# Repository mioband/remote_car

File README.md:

# remote_car
Данный репозиторий содержит код для модуля машинки для управления с браслета
## Ветки
В данном репозитории две основные ветки:
### main
Главная ветка со стабильной версией ПО. Здесь всегда должен быть чистый и рабочий код, а также вся документация. 
### develop
Ветка разработки. Здесь находятся тестовые и разрабатываемые версии кода.

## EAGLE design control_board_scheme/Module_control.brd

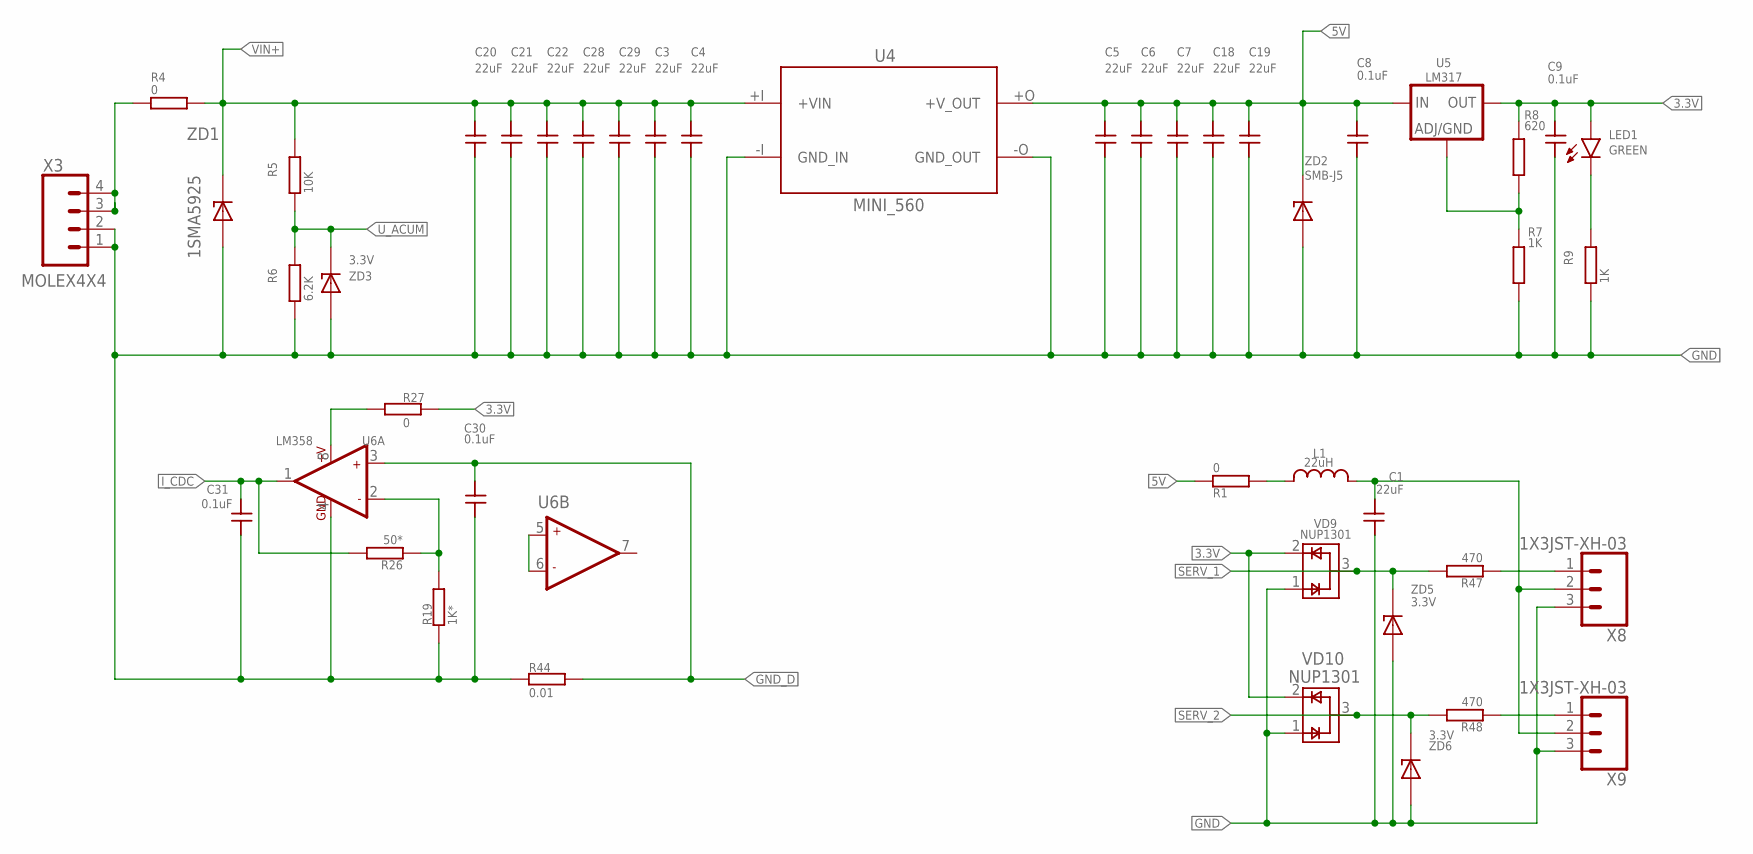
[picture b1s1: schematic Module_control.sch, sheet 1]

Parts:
C1, C3, C4, C5, C6, C7, C18, C19, C20, C21, C22, C28, C29: 22uF; 1206; VOLTAGE 16V
C8, C9, C30, C31: 0.1uF; 0603; VOLTAGE 16V
L1: 22uH; 0420CDMC
LED1: GREEN; 1608
R1, R27: 0; 0603
R4: 0; 2512
R5: 10K; 0603
R6: 6.2K; 0603
R7, R9: 1K; 0603
R8: 620; 0603
R19: 1K*; 0603
R26: 50*; 0603
R44: 0.01; 1206
R47, R48: 470; 0603
U4: MINI_560; MINI560_OTB
U5: LM317; D-PAK
U6: LM358; SOIC-8
VD9, VD10: NUP1301; SOT23
X3: MOLEX4X4; MOLEX-2X2U
X8, X9: 1X3JST-XH-03; JST-XH-03
ZD1: 1SMA5925; SMB
ZD2: SMB-J5; SMB
ZD3, ZD5, ZD6: 3.3V; MINIMELF

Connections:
3.3V: C9.P$2, LED1.P$2 (A), R8.P$2, R27.P$2, U5.4 (OUT), VD9.2 (VCC), VD10.2 (VCC); also elsewhere on the board
5: L1.2, R1.P$2
5V: C5.P$2, C6.P$2, C7.P$2, C8.P$2, C18.P$2, C19.P$2, R1.P$1, U4.+O (+V_OUT), U5.3 (IN), ZD2.C; also elsewhere on the board
GND: C1.P$1, C3.P$1, C4.P$1, C5.P$1, C6.P$1, C7.P$1, C8.P$1, C9.P$1, C18.P$1, C19.P$1, C20.P$1, C21.P$1, C22.P$1, C28.P$1, C29.P$1, C30.P$1, C31.P$1, R6.P$1, R7.P$2, R9.P$1, R19.P$1, R44.P$1, U4.-I (GND_IN), U4.-O (GND_OUT), U6.4 (GND), VD9.1 (GND), VD10.1 (GND), X3.1, X3.2, X8.3, X9.3, ZD1.A, ZD2.A, ZD3.A, ZD5.A, ZD6.A; also elsewhere on the board
GND_D: C30.P$2, R44.P$2, U6.3 (+IN1); also elsewhere on the board
I_CDC: C31.P$2, R26.P$2, U6.1 (OUT1); also elsewhere on the board
unnamed: R48.P$1, X9.1
unnamed: R7.P$1, R8.P$1, U5.1 (ADJ/GND)
unnamed: LED1.P$1 (C), R9.P$2
unnamed: R4.1, X3.3, X3.4
unnamed: R47.P$1, X8.1
unnamed: R19.P$2, R26.P$1, U6.2 (-IN1)
unnamed: U6.5 (+IN2), U6.6 (-IN2)
SERV_1: R47.P$2, VD9.3 (I/O), ZD5.C; also elsewhere on the board
SERV_2: R48.P$2, VD10.3 (I/O), ZD6.C; also elsewhere on the board
U_ACUM: R5.P$1, R6.P$2, ZD3.C; also elsewhere on the board
V+: R27.P$1, U6.8 (+V)
VIN+: C3.P$2, C4.P$2, C20.P$2, C21.P$2, C22.P$2, C28.P$2, C29.P$2, R4.2, R5.P$2, U4.+I (+VIN), ZD1.C; also elsewhere on the board
VSERV: C1.P$2, L1.1, X8.2, X9.2

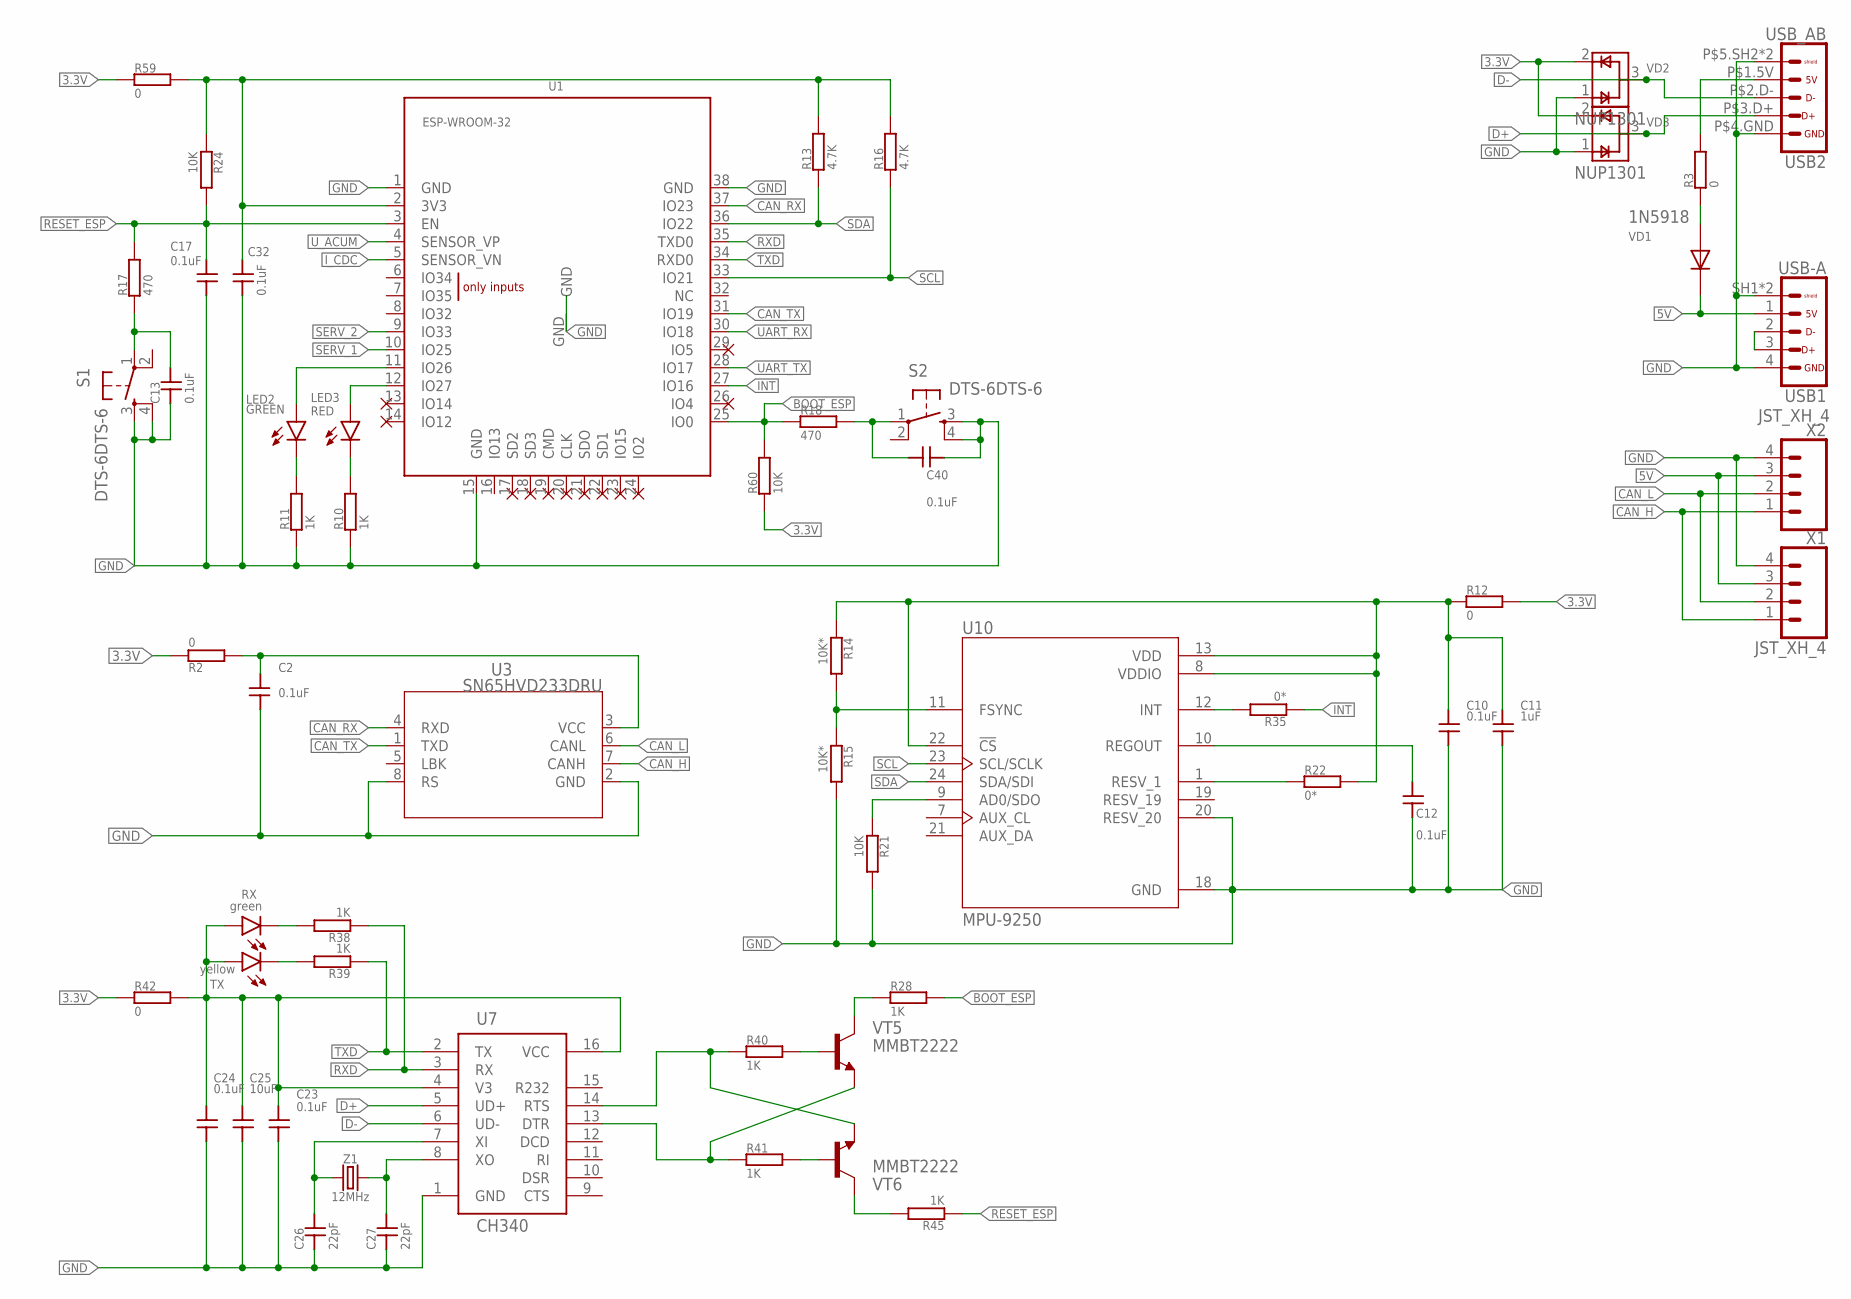
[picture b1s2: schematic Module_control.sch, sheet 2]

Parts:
C2, C10, C12, C13, C17, C23, C24, C32, C40: 0.1uF; 0603; VOLTAGE 16V
C11: 1uF; 0603; VOLTAGE 16V
C25: 10uF; 0603; VOLTAGE 16V
C26, C27: 22pF; 0603; VOLTAGE 6.3V
LED2: GREEN; 1608
LED3: RED; 1608
R2, R3, R12, R42, R59: 0; 0603
R10, R11, R28, R38, R39, R40, R41, R45: 1K; 0603
R13, R16: 4.7K; 0603
R14, R15: 10K*; 0603
R17, R18: 470; 0603
R21, R24, R60: 10K; 0603
R22, R35: 0*; 0603
RX: green; 2013
S1, S2: DTS-6DTS-6; DTS-6
TX: yellow; 2013
U1: ESP-WROOM-32
U3: SN65HVD233DRU; SOIC-8
U7: CH340; SOIC-16
U10: MPU-9250; QFN40P300X300X105-24N
USB1: USB-A; A-VERTICAL
USB2: USB_AB; B-VERTICAL
VD1: 1N5918; SOD123
VD2, VD3: NUP1301; SOT23
VT5, VT6: MMBT2222; SOT-23
X1, X2: JST_XH_4; JST-XH-04
Z1: 12MHz; CRYSTAL-SMD-3.2X2.5MM

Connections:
3.3V: R2.P$1, R12.P$2, R42.P$1, R59.P$1, R60.P$1, VD2.2 (VCC), VD3.2 (VCC); also elsewhere on the board
5V: USB1.1, VD1.C, X1.3, X2.3; also elsewhere on the board
+3.3: C2.P$2, R2.P$2, U3.3 (VCC)
+3V: C10.P$2, C11.P$2, R12.P$1, R14.P$1, R22.P$2, U10.8 (VDDIO), U10.13 (VDD), U10.22 (!CS)
BOOT_ESP: R18.P$1, R28.P$2, R60.P$2, U1.25 (IO0)
CAN_H: U3.7 (CANH), X1.1, X2.1
CAN_L: U3.6 (CANL), X1.2, X2.2
CAN_RX: U1.37 (IO23), U3.4 (RXD)
CAN_TX: U1.31 (IO19), U3.1 (TXD)
D+: U7.5 (UD+), USB2.P$3.D+ (3), VD3.3 (I/O)
D-: U7.6 (UD-), USB2.P$2.D- (2), VD2.3 (I/O)
DTR: R41.P$1, U7.13 (DTR), VT5.2 (E)
ESP_3.3V: C32.P$2, R13.P$2, R16.P$2, R24.P$1, R59.P$2, U1.2 (3V3)
GND: C2.P$1, C10.P$1, C11.P$1, C12.P$1, C13.P$1, C17.P$1, C23.P$1, C24.P$1, C25.P$1, C26.P$1, C27.P$1, C32.P$1, C40.P$1, R10.P$1, R11.P$1, R15.P$2, R21.P$2, S1.3, S1.4, S2.3, S2.4, U1.1 (GND), U1.15 (GND), U1.38 (GND), U1.GND, U3.2 (GND), U3.8 (RS), U7.1 (GND), U10.18 (GND), U10.20 (RESV_20), USB1.4, USB1.SH1 (SHIELD), USB1.SH2 (SHIELD), USB2.P$4.GND (4), USB2.P$5.SH2 (SHIELD), USB2.P$6.SH1 (SHIELD), VD2.1 (GND), VD3.1 (GND), X1.4, X2.4; also elsewhere on the board
INT: R35.P$1, U1.27 (IO16)
IT: R35.P$2, U10.12 (INT)
I_CDC: U1.5 (SENSOR_VN); also elsewhere on the board
unnamed: C40.P$2, R18.P$2, S2.1
unnamed: R3.P$2, USB2.P$1.5V (1)
unnamed: USB1.2, USB1.3
unnamed: R3.P$1, VD1.A
unnamed: LED2.P$2 (A), U1.11 (IO26)
unnamed: LED3.P$2 (A), U1.12 (IO27)
unnamed: LED3.P$1 (C), R10.P$2
unnamed: LED2.P$1 (C), R11.P$2
unnamed: R21.P$1, U10.9 (AD0/SDO)
unnamed: C12.P$2, U10.10 (REGOUT)
unnamed: R22.P$1, U10.1 (RESV_1)
unnamed: R38.P$2, RX.P$1 (C)
unnamed: R14.P$2, R15.P$1, U10.11 (FSYNC)
unnamed: R39.P$2, TX.P$1 (C)
unnamed: C27.P$2, U7.8 (XO), Z1.3 (2)
unnamed: C26.P$2, U7.7 (XI), Z1.1
unnamed: R40.P$2, VT5.1 (B)
unnamed: R41.P$2, VT6.1 (B)
unnamed: R28.P$1, VT5.3 (C)
unnamed: R45.P$2, VT6.3 (C)
unnamed: C13.P$2, R17.P$1, S1.1
RESET_ESP: C17.P$2, R17.P$2, R24.P$2, R45.P$1, U1.3 (EN)
RTS: R40.P$1, U7.14 (RTS), VT6.2 (E)
RXD: R38.P$1, U1.35 (TXD0), U7.3 (RX)
SCL: R16.P$1, U1.33 (IO21), U10.23 (SCL/SCLK)
SDA: R13.P$1, U1.36 (IO22), U10.24 (SDA/SDI)
SERV_1: U1.10 (IO25); also elsewhere on the board
SERV_2: U1.9 (IO33); also elsewhere on the board
TXD: R39.P$1, U1.34 (RXD0), U7.2 (TX)
UART_RX: U1.30 (IO18); also elsewhere on the board
UART_TX: U1.28 (IO17); also elsewhere on the board
U_ACUM: U1.4 (SENSOR_VP); also elsewhere on the board
VCC: C23.P$2, C24.P$2, C25.P$2, R42.P$2, RX.P$2 (A), TX.P$2 (A), U7.4 (V3), U7.16 (VCC)

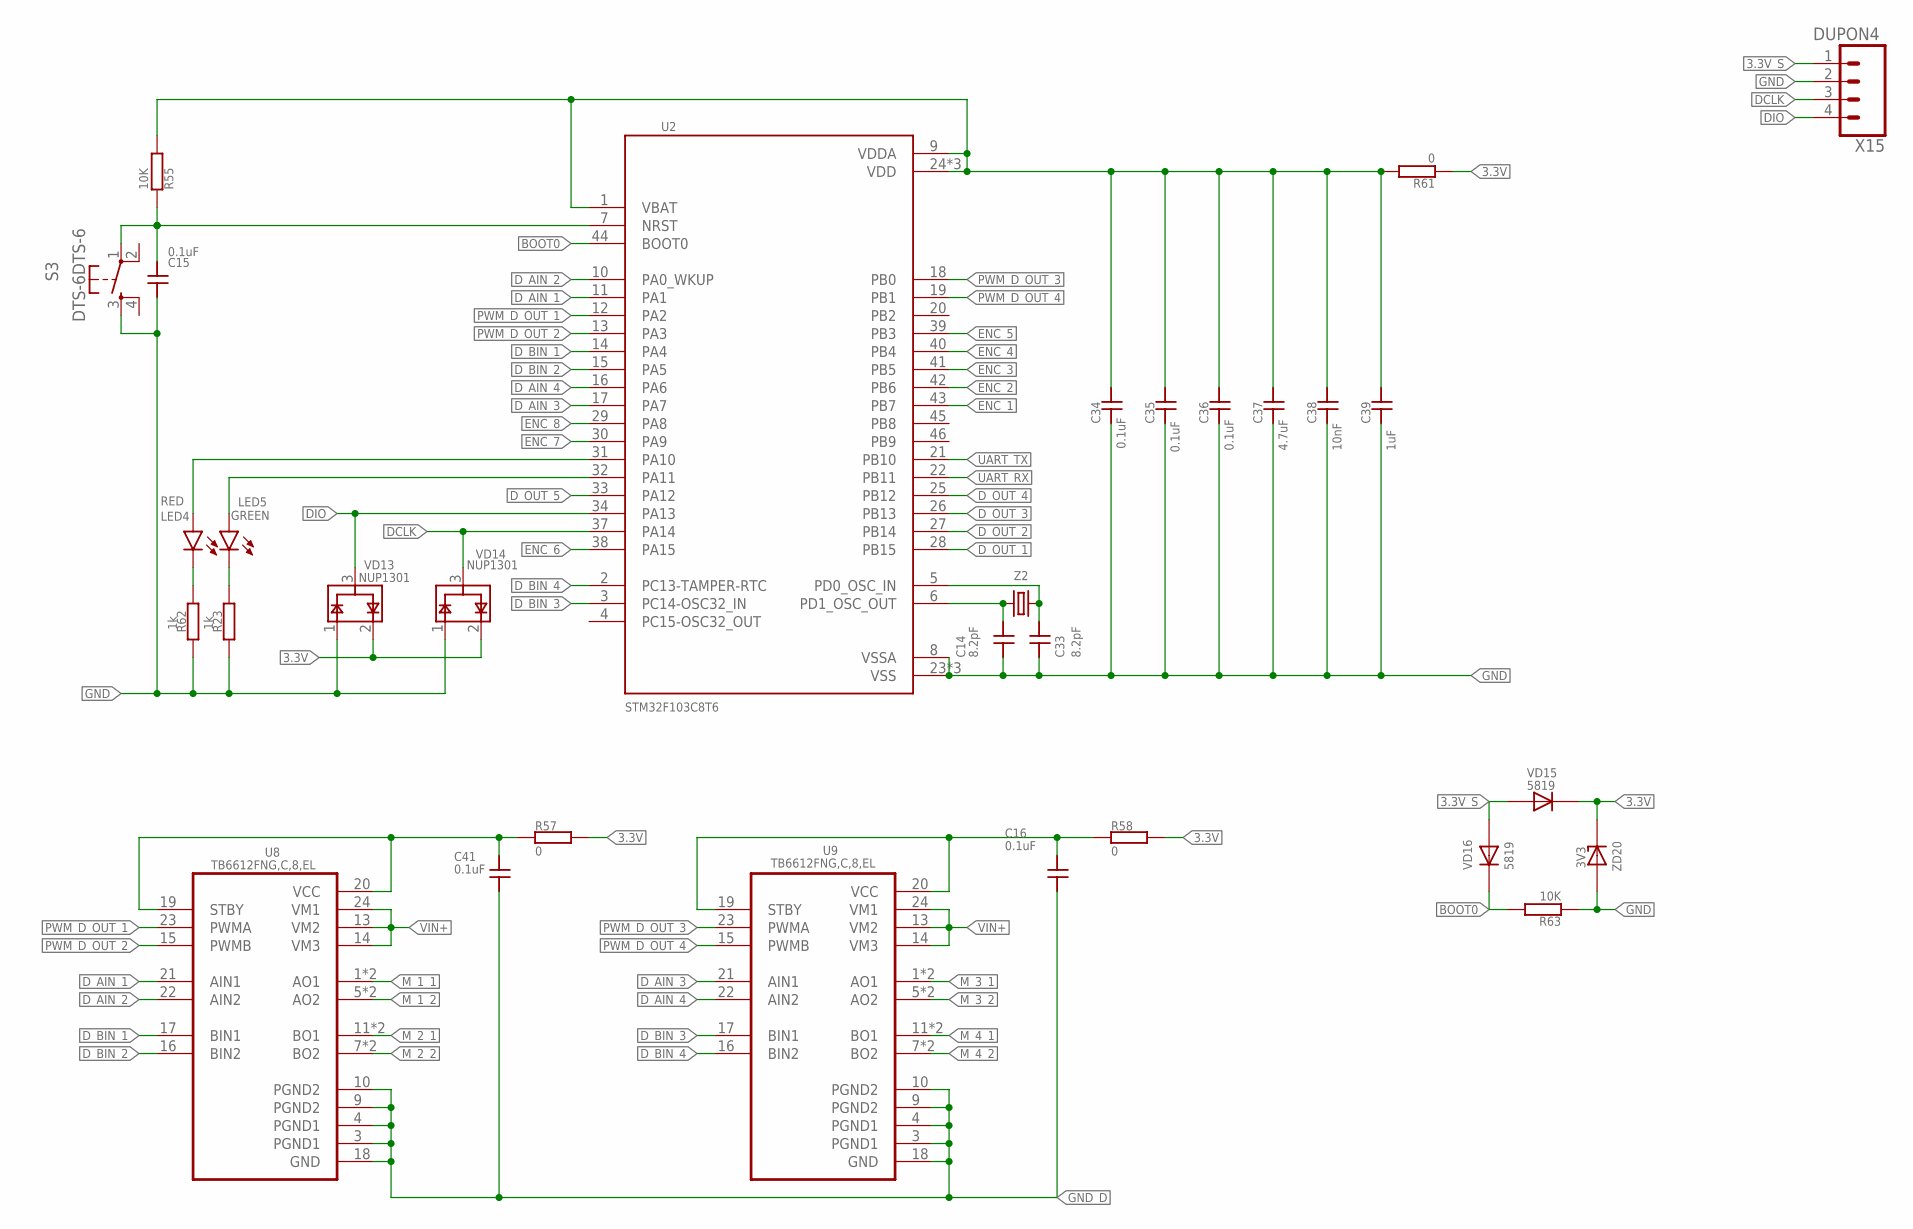
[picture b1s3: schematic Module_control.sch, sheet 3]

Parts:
C14, C33: 8.2pF; 0603; VOLTAGE 16V
C15, C16, C34, C35, C36, C41: 0.1uF; 0603; VOLTAGE 16V
C37: 4.7uF; 0603; VOLTAGE 16V
C38: 10nF; 0603; VOLTAGE 16V
C39: 1uF; 0603; VOLTAGE 16V
LED4: RED; 1608
LED5: GREEN; 1608
R23, R62: 1k; 0603
R55, R63: 10K; 0603
R57, R58, R61: 0; 0603
S3: DTS-6DTS-6; DTS-6
U2: STM32F103C8T6; QFP50P900X900X160-48N
U8, U9: TB6612FNG,C,8,EL; SOP65
VD13, VD14: NUP1301; SOT23
VD15, VD16: 5819; SOD123
X15: DUPON4; 1X04DUPON
Z2: 8MHz; CRYSTAL-SMD-3.2X2.5MM
ZD20: 3V3; MINIMELF

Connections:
3.3V: R57.P$2, R58.P$2, R61.P$1, VD13.2 (VCC), VD14.2 (VCC), VD15.C, ZD20.C; also elsewhere on the board
3.3V_S: VD15.A, VD16.A, X15.1
+VC: C41.P$2, R57.P$1, U8.19 (STBY), U8.20 (VCC)
BOOT0: R63.P$2, U2.44 (BOOT0), VD16.C
DCLK: U2.37 (PA14), VD14.3 (I/O), X15.3
DIO: U2.34 (PA13), VD13.3 (I/O), X15.4
D_AIN_1: U2.11 (PA1), U8.21 (AIN1)
D_AIN_2: U2.10 (PA0_WKUP), U8.22 (AIN2)
D_AIN_3: U2.17 (PA7), U9.21 (AIN1)
D_AIN_4: U2.16 (PA6), U9.22 (AIN2)
D_BIN_1: U2.14 (PA4), U8.17 (BIN1)
D_BIN_2: U2.15 (PA5), U8.16 (BIN2)
D_BIN_3: U2.3 (PC14-OSC32_IN), U9.17 (BIN1)
D_BIN_4: U2.2 (PC13-TAMPER-RTC), U9.16 (BIN2)
D_OUT_1: U2.28 (PB15); also elsewhere on the board
D_OUT_2: U2.27 (PB14); also elsewhere on the board
D_OUT_3: U2.26 (PB13); also elsewhere on the board
D_OUT_4: U2.25 (PB12); also elsewhere on the board
D_OUT_5: U2.33 (PA12); also elsewhere on the board
ENC_1: U2.43 (PB7); also elsewhere on the board
ENC_2: U2.42 (PB6); also elsewhere on the board
ENC_3: U2.41 (PB5); also elsewhere on the board
ENC_4: U2.40 (PB4); also elsewhere on the board
ENC_5: U2.39 (PB3); also elsewhere on the board
ENC_6: U2.38 (PA15); also elsewhere on the board
ENC_7: U2.30 (PA9); also elsewhere on the board
ENC_8: U2.29 (PA8); also elsewhere on the board
GND: C14.P$1, C15.P$2, C33.P$1, C34.P$1, C35.P$1, C36.P$1, C37.P$1, C38.P$1, C39.P$1, R23.P$2, R62.P$2, R63.P$1, S3.3, U2.8 (VSSA), U2.23 (VSS), U2.35 (VSS), U2.47 (VSS), VD13.1 (GND), VD14.1 (GND), X15.2, ZD20.A; also elsewhere on the board
GND_D: C16.P$1, C41.P$1, U8.3 (PGND1), U8.4 (PGND1), U8.9 (PGND2), U8.10 (PGND2), U8.18 (GND), U9.3 (PGND1), U9.4 (PGND1), U9.9 (PGND2), U9.10 (PGND2), U9.18 (GND); also elsewhere on the board
M_1_1: U8.1 (AO1), U8.2 (AO1); also elsewhere on the board
M_1_2: U8.5 (AO2), U8.6 (AO2); also elsewhere on the board
M_2_1: U8.11 (BO1), U8.12 (BO1); also elsewhere on the board
M_2_2: U8.7 (BO2), U8.8 (BO2); also elsewhere on the board
M_3_1: U9.1 (AO1), U9.2 (AO1); also elsewhere on the board
M_3_2: U9.5 (AO2), U9.6 (AO2); also elsewhere on the board
M_4_1: U9.11 (BO1), U9.12 (BO1); also elsewhere on the board
M_4_2: U9.7 (BO2), U9.8 (BO2); also elsewhere on the board
unnamed: LED4.P$1 (C), R62.P$1
unnamed: C16.P$2, R58.P$1, U9.19 (STBY), U9.20 (VCC)
unnamed: LED5.P$1 (C), R23.P$1
unnamed: LED4.P$2 (A), U2.31 (PA10)
unnamed: LED5.P$2 (A), U2.32 (PA11)
unnamed: C14.P$2, U2.6 (PD1_OSC_OUT), Z2.1
unnamed: C33.P$2, U2.5 (PD0_OSC_IN), Z2.3 (2)
NRST: C15.P$1, R55.P$1, S3.1, U2.7 (NRST)
PWM_D_OUT_1: U2.12 (PA2), U8.23 (PWMA)
PWM_D_OUT_2: U2.13 (PA3), U8.15 (PWMB)
PWM_D_OUT_3: U2.18 (PB0), U9.23 (PWMA)
PWM_D_OUT_4: U2.19 (PB1), U9.15 (PWMB)
UART_RX: U2.22 (PB11); also elsewhere on the board
UART_TX: U2.21 (PB10); also elsewhere on the board
VDD1: C34.P$2, C35.P$2, C36.P$2, C37.P$2, C38.P$2, C39.P$2, R55.P$2, R61.P$2, U2.1 (VBAT), U2.9 (VDDA), U2.24 (VDD), U2.36 (VDD), U2.48 (VDD)
VIN+: U8.13 (VM2), U8.14 (VM3), U8.24 (VM1), U9.13 (VM2), U9.14 (VM3), U9.24 (VM1); also elsewhere on the board

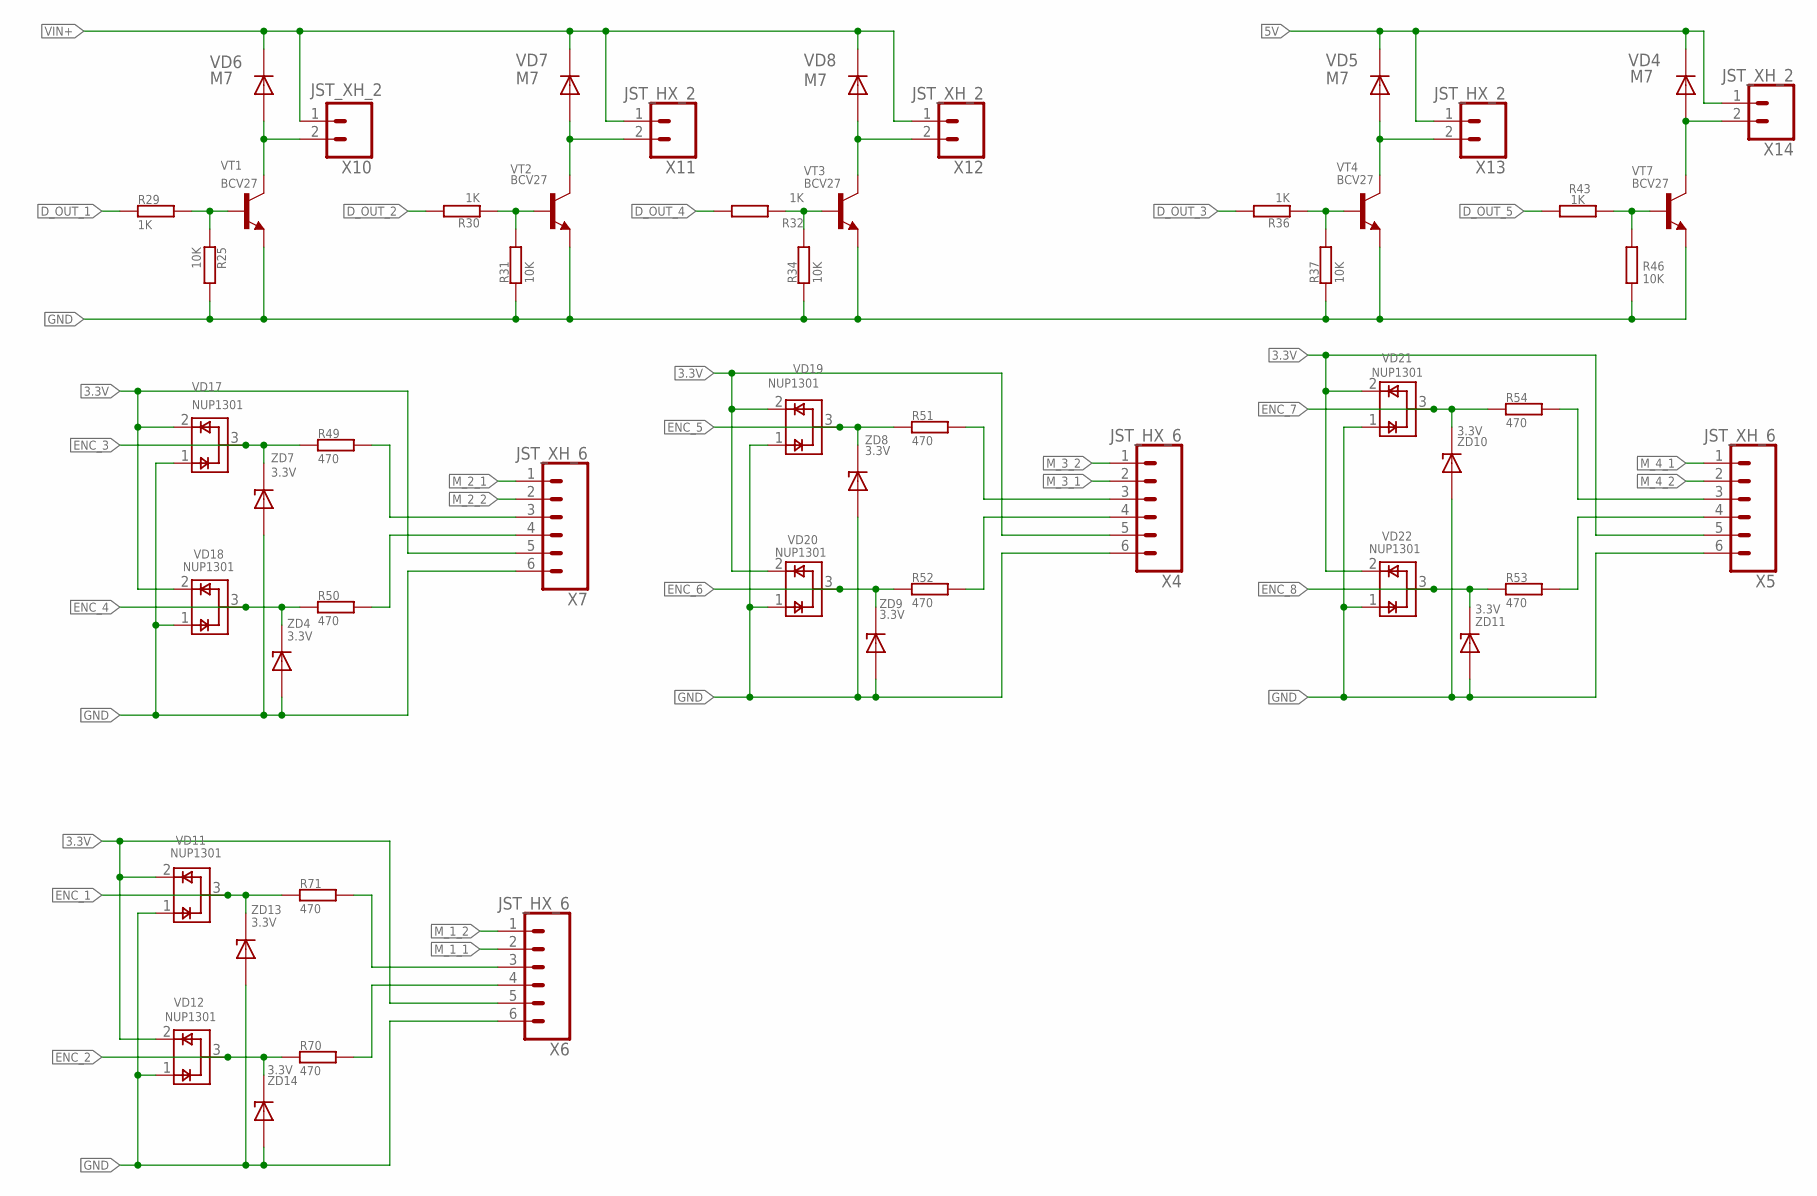
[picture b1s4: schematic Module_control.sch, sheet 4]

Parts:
R25, R31, R34, R37, R46: 10K; 0603
R29, R30, R32, R36, R43: 1K; 0603
R49, R50, R51, R52, R53, R54, R70, R71: 470; 0603
VD4, VD5, VD6, VD7, VD8: M7; SMA
VD11, VD12, VD17, VD18, VD19, VD20, VD21, VD22: NUP1301; SOT23
VT1, VT2, VT3, VT4, VT7: BCV27; SOT-23
X4, X6: JST_HX_6; JST-XH-06
X5, X7: JST_XH_6; JST-XH-06
X10, X12, X14: JST_XH_2; JST-XH-02
X11, X13: JST_HX_2; JST-XH-02
ZD4, ZD7, ZD8, ZD9, ZD10, ZD11, ZD13, ZD14: 3.3V; MINIMELF

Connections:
3.3V: VD11.2 (VCC), VD12.2 (VCC), VD17.2 (VCC), VD18.2 (VCC), VD19.2 (VCC), VD20.2 (VCC), VD21.2 (VCC), VD22.2 (VCC), X4.5, X5.5, X6.5, X7.5; also elsewhere on the board
5V: VD4.C, VD5.C, X13.1, X14.1; also elsewhere on the board
D_OUT_1: R29.P$1; also elsewhere on the board
D_OUT_2: R30.P$2; also elsewhere on the board
D_OUT_3: R36.P$2; also elsewhere on the board
D_OUT_4: R32.P$2; also elsewhere on the board
D_OUT_5: R43.P$2; also elsewhere on the board
ENC1: R71.P$2, X6.3
ENC2: R70.P$2, X6.4
ENC3: R49.P$2, X7.3
ENC4: R50.P$2, X7.4
ENC5: R51.P$2, X4.3
ENC6: R52.P$2, X4.4
ENC7: R54.P$2, X5.3
ENC8: R53.P$2, X5.4
ENC_1: R71.P$1, VD11.3 (I/O), ZD13.C; also elsewhere on the board
ENC_2: R70.P$1, VD12.3 (I/O), ZD14.C; also elsewhere on the board
ENC_3: R49.P$1, VD17.3 (I/O), ZD7.C; also elsewhere on the board
ENC_4: R50.P$1, VD18.3 (I/O), ZD4.C; also elsewhere on the board
ENC_5: R51.P$1, VD19.3 (I/O), ZD8.C; also elsewhere on the board
ENC_6: R52.P$1, VD20.3 (I/O), ZD9.C; also elsewhere on the board
ENC_7: R54.P$1, VD21.3 (I/O), ZD10.C; also elsewhere on the board
ENC_8: R53.P$1, VD22.3 (I/O), ZD11.C; also elsewhere on the board
GND: R25.P$2, R31.P$1, R34.P$1, R37.P$1, R46.P$1, VD11.1 (GND), VD12.1 (GND), VD17.1 (GND), VD18.1 (GND), VD19.1 (GND), VD20.1 (GND), VD21.1 (GND), VD22.1 (GND), VT1.2 (E), VT2.2 (E), VT3.2 (E), VT4.2 (E), VT7.2 (E), X4.6, X5.6, X6.6, X7.6, ZD4.A, ZD7.A, ZD8.A, ZD9.A, ZD10.A, ZD11.A, ZD13.A, ZD14.A; also elsewhere on the board
M_1_1: X6.2; also elsewhere on the board
M_1_2: X6.1; also elsewhere on the board
M_2_1: X7.1; also elsewhere on the board
M_2_2: X7.2; also elsewhere on the board
M_3_1: X4.2; also elsewhere on the board
M_3_2: X4.1; also elsewhere on the board
M_4_1: X5.1; also elsewhere on the board
M_4_2: X5.2; also elsewhere on the board
unnamed: R25.P$1, R29.P$2, VT1.1 (B)
unnamed: VD6.A, VT1.3 (C), X10.2
unnamed: R30.P$1, R31.P$2, VT2.1 (B)
unnamed: R36.P$1, R37.P$2, VT4.1 (B)
unnamed: VD7.A, VT2.3 (C), X11.2
unnamed: VD8.A, VT3.3 (C), X12.2
unnamed: VD5.A, VT4.3 (C), X13.2
unnamed: R32.P$1, R34.P$2, VT3.1 (B)
unnamed: R43.P$1, R46.P$2, VT7.1 (B)
unnamed: VD4.A, VT7.3 (C), X14.2
VIN+: VD6.C, VD7.C, VD8.C, X10.1, X11.1, X12.1; also elsewhere on the board

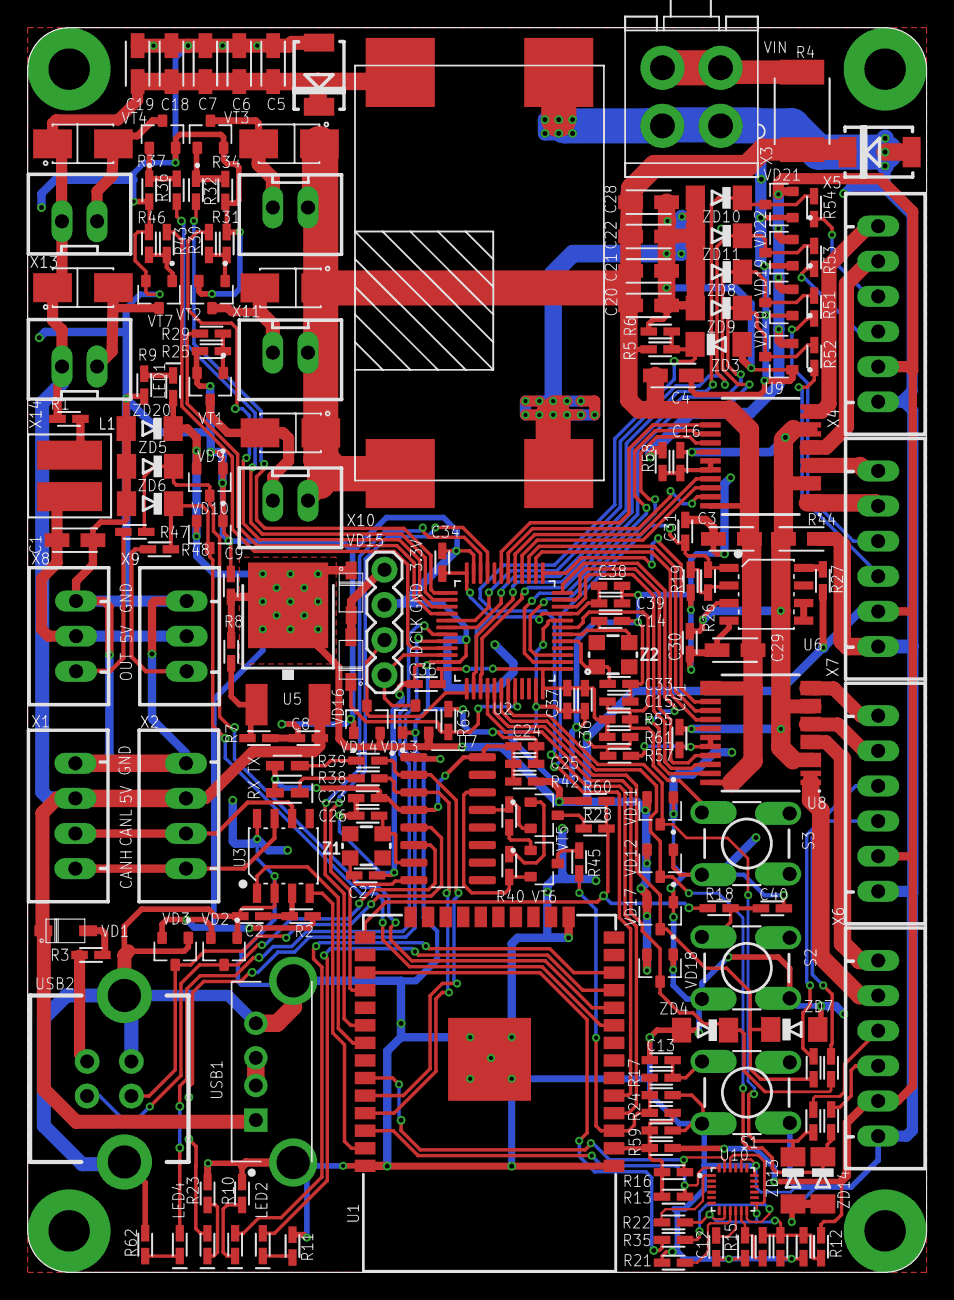
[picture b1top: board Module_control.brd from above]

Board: 2 copper layers, 65.0 x 90.0 mm, 186 parts (0 on the bottom side), 127 nets.

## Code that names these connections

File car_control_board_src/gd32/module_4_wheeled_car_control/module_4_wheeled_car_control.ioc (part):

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Mcu.Name=STM32F103C(8-B)Tx
Mcu.Package=LQFP48
Mcu.UserName=STM32F103C8Tx
PA0-WKUP.GPIOParameters=GPIO_Label
PA0-WKUP.GPIO_Label=DIG_AIN_2
PA0-WKUP.Signal=GPIO_Output
PA1.GPIOParameters=GPIO_Label
PA1.GPIO_Label=DIG_AIN_1
PA1.Signal=GPIO_Output
PA10.GPIOParameters=GPIO_Label
PA10.GPIO_Label=LED_2
PA10.Signal=GPIO_Output
PA11.GPIOParameters=GPIO_Label
PA11.GPIO_Label=LED_1
PA11.Signal=GPIO_Output
PA12.GPIOParameters=GPIO_Label
PA12.GPIO_Label=DIG_OUT_5
PA12.Signal=GPIO_Output
PA13.Mode=Serial_Wire
PA13.Signal=SYS_JTMS-SWDIO
PA14.Mode=Serial_Wire
PA14.Signal=SYS_JTCK-SWCLK
PA15.GPIOParameters=GPIO_Label
PA15.GPIO_Label=ENC_6
PA15.Signal=GPIO_Input
PA2.Signal=S_TIM2_CH3
PA3.Signal=S_TIM2_CH4
PA4.GPIOParameters=GPIO_Label
PA4.GPIO_Label=DIG_BIN_1
PA4.Signal=GPIO_Output
PA5.GPIOParameters=GPIO_Label
PA5.GPIO_Label=DIG_BIN_2
PA5.Signal=GPIO_Output
PA6.GPIOParameters=GPIO_Label
PA6.GPIO_Label=DIG_AIN_4
PA6.Signal=GPIO_Output
PA7.GPIOParameters=GPIO_Label
PA7.GPIO_Label=DIG_AIN_3
PA7.Signal=GPIO_Output
PA8.GPIOParameters=GPIO_Label
PA8.GPIO_Label=ENC_8
PA8.Signal=GPIO_Input
PA9.GPIOParameters=GPIO_Label
PA9.GPIO_Label=ENC_7
PA9.Signal=GPIO_Input
PB0.Signal=S_TIM3_CH3
PB1.Signal=S_TIM3_CH4
PB10.Mode=Asynchronous
PB10.Signal=USART3_TX
PB11.Mode=Asynchronous
PB11.Signal=USART3_RX
PB12.GPIOParameters=GPIO_Label
PB12.GPIO_Label=DIG_OUT_4
PB12.Signal=GPIO_Output
PB13.GPIOParameters=GPIO_Label
PB13.GPIO_Label=DIG_OUT_3
PB13.Signal=GPIO_Output
PB14.GPIOParameters=GPIO_Label
PB14.GPIO_Label=DIG_OUT_2
PB14.Signal=GPIO_Output
PB15.GPIOParameters=GPIO_Label
PB15.GPIO_Label=DIG_OUT_1
PB15.Signal=GPIO_Output
PB3.GPIOParameters=GPIO_Label
PB3.GPIO_Label=ENC_5
PB3.Signal=GPIO_Input
PB4.GPIOParameters=GPIO_Label
PB4.GPIO_Label=ENC_4
PB4.Signal=GPIO_Input
PB5.GPIOParameters=GPIO_Label
PB5.GPIO_Label=ENC_3
PB5.Signal=GPIO_Input
PB6.GPIOParameters=GPIO_Label
PB6.GPIO_Label=ENC_2
PB6.Signal=GPIO_Input
PB7.GPIOParameters=GPIO_Label
PB7.GPIO_Label=ENC_1
PB7.Signal=GPIO_Input
PC13-TAMPER-RTC.GPIOParameters=GPIO_Label
PC13-TAMPER-RTC.GPIO_Label=DIG_BIN_4
PC13-TAMPER-RTC.Signal=GPIO_Output
PC14-OSC32_IN.GPIOParameters=GPIO_Label
PC14-OSC32_IN.GPIO_Label=DIG_BIN_3
PC14-OSC32_IN.Signal=GPIO_Output
board=custom

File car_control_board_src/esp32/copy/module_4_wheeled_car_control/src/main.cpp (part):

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
// /* Analog pins */
// #define U_ACCUM     GPIO_NUM_36
// #define I_CDC       GPIO_NUM_39
// /* LEDs */
// #define LED_2       GPIO_NUM_26
// #define LED_3       GPIO_NUM_27
// /* UART pins */
// #define UART_TX     GPIO_NUM_18
// #define UART_RX     GPIO_NUM_17


// uint8_t buf_command[10];
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//     while(!Serial1);

//     pinMode(U_ACCUM, ANALOG);
//     pinMode(I_CDC, ANALOG);
//     pinMode(LED_2, OUTPUT);
//     pinMode(LED_3, OUTPUT);
// }
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///////////////////////////////////////////////////////////////
uint8_t flag = 0;

constexpr uint8_t UART_TX_PIN = GPIO_NUM_17;
constexpr uint8_t UART_RX_PIN = GPIO_NUM_16;
constexpr uint32_t UART_BAUD = 38400;

int buff_char[6];

/* Analog pins */
#define U_ACCUM     GPIO_NUM_36
#define I_CDC       GPIO_NUM_39
/* LEDs */
#define LED_2       GPIO_NUM_26
#define LED_3       GPIO_NUM_27
/* UART pins */
#define UART_TX     GPIO_NUM_18
#define UART_RX     GPIO_NUM_17


uint8_t buf_command[10];
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  while(!Serial1);

  pinMode(U_ACCUM, ANALOG);
  pinMode(I_CDC, ANALOG);
  pinMode(LED_2, OUTPUT);
  pinMode(LED_3, OUTPUT);
}
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
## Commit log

2022-08-22 add sample stable code
2022-08-22 add sample unstable code to branch develop
2022-08-22 added control board schemes
2022-08-22 added gd32 test code
2022-08-23 added esp32 test code
2022-08-25 esp32 test code update
2022-08-25 gd32 test code update
2022-10-04 green tank
2022-10-24 comments were added
2022-11-10 gd32 code upd
